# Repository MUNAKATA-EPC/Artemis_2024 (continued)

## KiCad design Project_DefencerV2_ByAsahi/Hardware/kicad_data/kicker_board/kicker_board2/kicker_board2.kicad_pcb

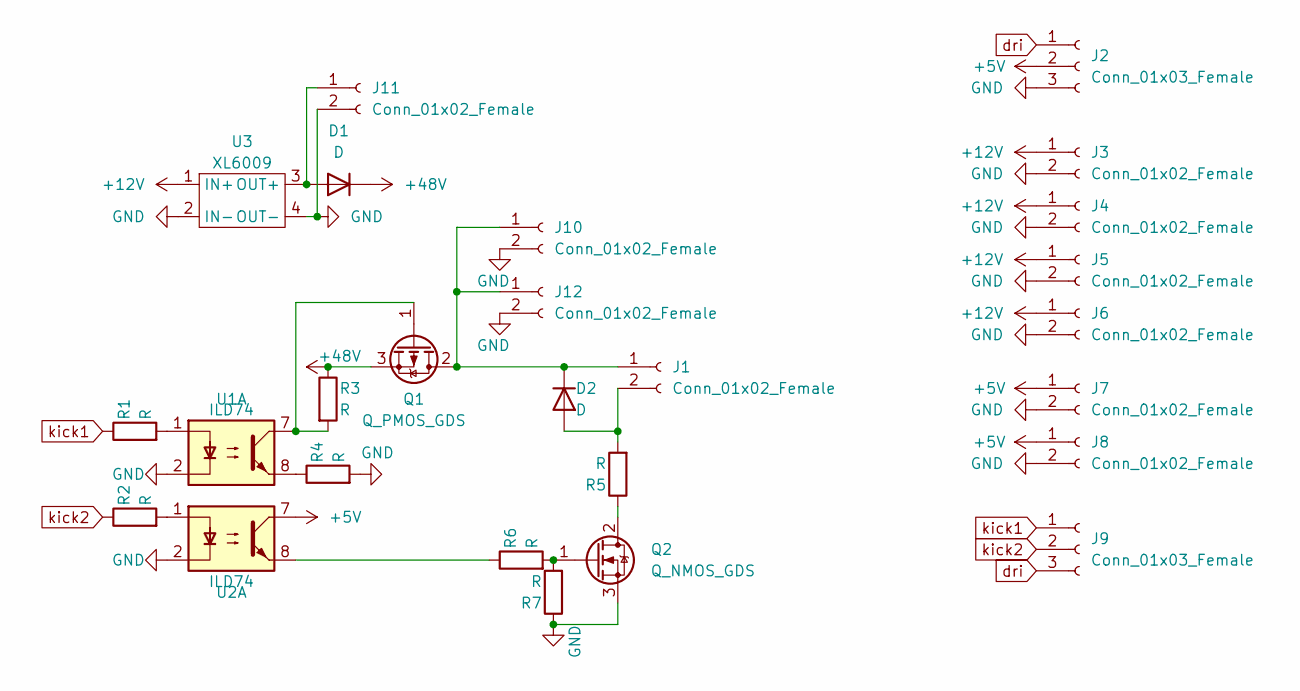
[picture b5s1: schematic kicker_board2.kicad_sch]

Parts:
D1, D2: D; D_5W_P10.16mm_Horizontal
J1, J3, J4, J5, J6, J7, J8, J10, J11, J12: Conn_01x02_Female; JST_XH_B2B-XH-A_1x02_P2.50mm_Vertical
J2, J9: Conn_01x03_Female; JST_XH_B3B-XH-A_1x03_P2.50mm_Vertical
Q1: Q_PMOS_GDS; Nch MOSFET
Q2: Q_NMOS_GDS; Nch MOSFET
R1, R2, R3, R4, R6, R7: R; R_Axial_DIN0204_L3.6mm_D1.6mm_P5.08mm_Horizontal
R5: R; R_Axial_Power_L25.0mm_W9.0mm_P10.16mm_Vertical
U1, U2: ILD74; フォトカプラー
U3: XL6009

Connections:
+5V: J2.2, J7.1, J8.1, U2.7
+12V: J3.1, J4.1, J5.1, J6.1, U3.1 (IN+)
+48V: D1.1 (K), Q1.3 (S), R3.1
GND: J2.3, J3.2, J4.2, J5.2, J6.2, J7.2, J8.2, J10.2, J11.2, J12.2, Q2.3 (S), R4.2, R7.1, U1.2, U2.2, U3.2 (IN-), U3.4 (OUT-)
unnamed: D1.2 (A), J11.1, U3.3 (OUT+)
unnamed: D2.1 (K), J1.1, J10.1, J12.1, Q1.2 (D)
unnamed: D2.2 (A), J1.2, R5.2
unnamed: Q1.1 (G), R3.2, U1.7
unnamed: Q2.1 (G), R6.2, R7.2
unnamed: Q2.2 (D), R5.1
unnamed: R1.2, U1.1
unnamed: R2.2, U2.1
unnamed: R4.1, U1.8
unnamed: R6.1, U2.8
dri: J2.1, J9.3
kick1: J9.1, R1.1
kick2: J9.2, R2.1

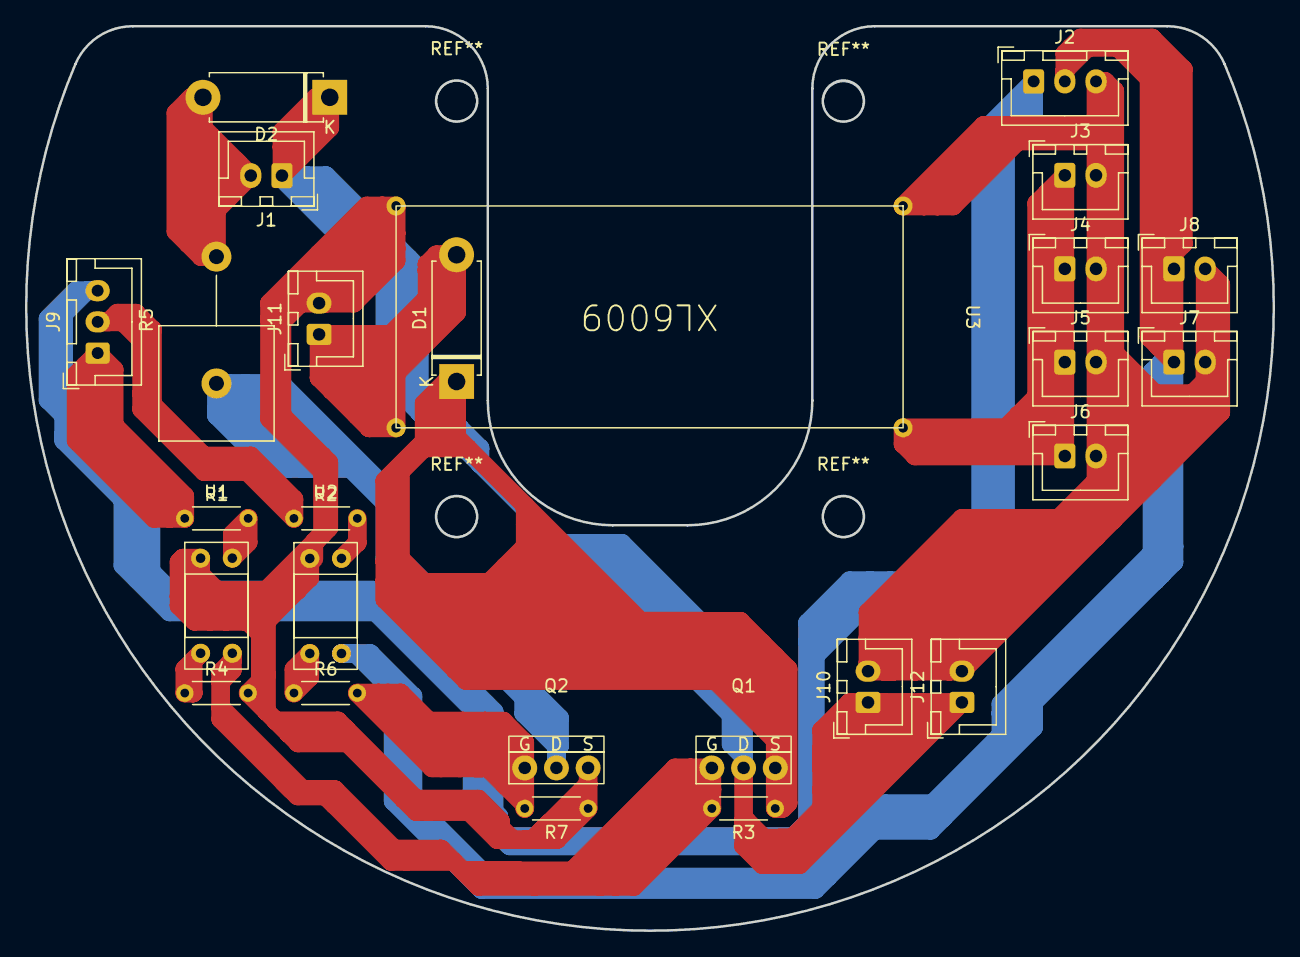
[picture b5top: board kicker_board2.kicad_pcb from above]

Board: 2 copper layers, 100.0 x 72.5 mm, 26 parts (0 on the bottom side), 17 nets.

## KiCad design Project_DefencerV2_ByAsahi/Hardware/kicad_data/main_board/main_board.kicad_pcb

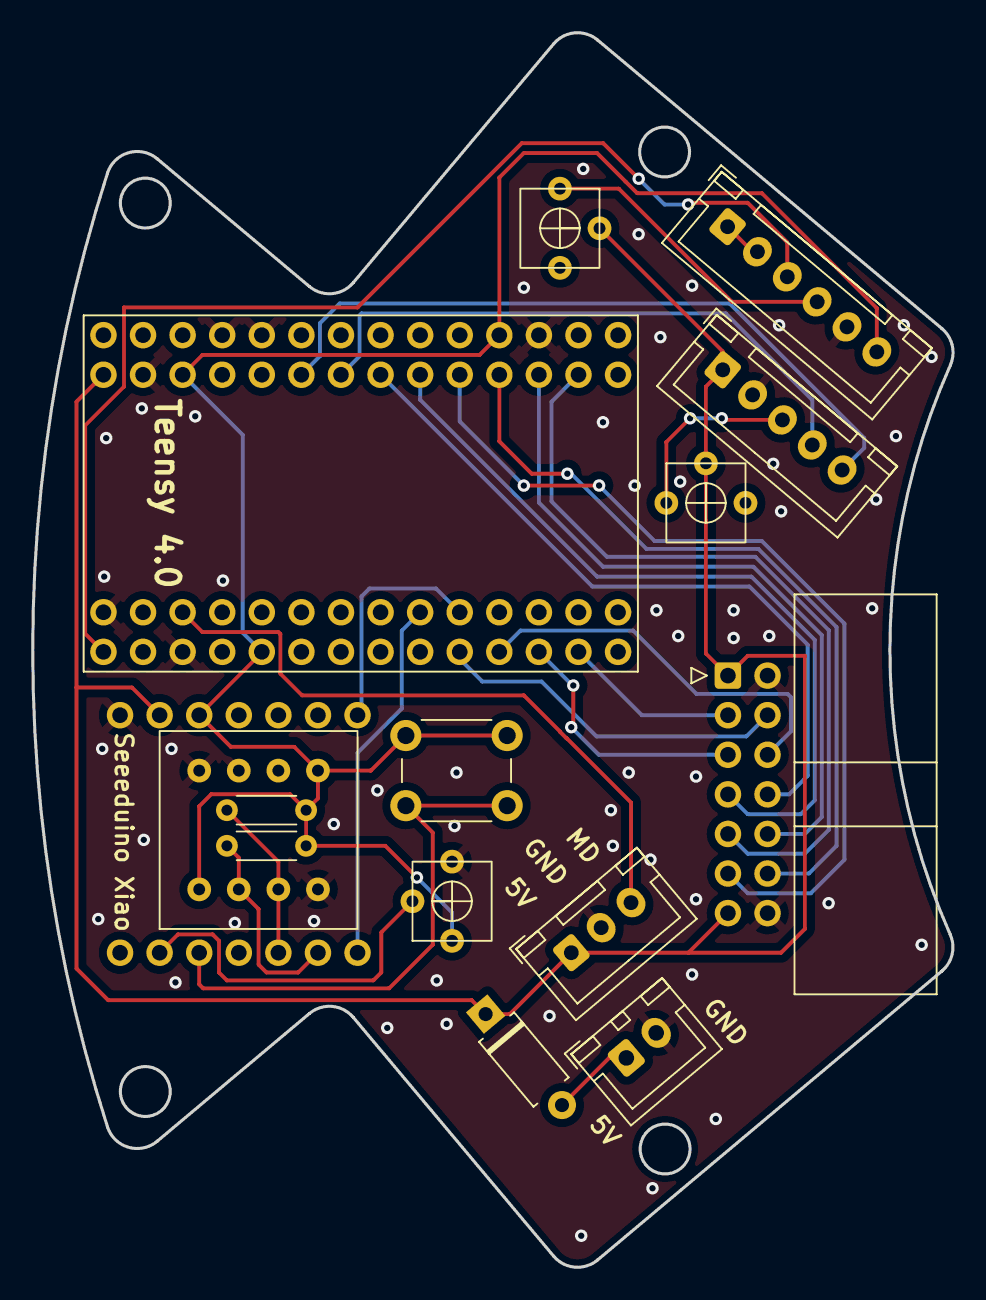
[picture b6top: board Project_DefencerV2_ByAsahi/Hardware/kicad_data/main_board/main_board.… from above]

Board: 2 copper layers, 59.1 x 79.2 mm, 15 parts (0 on the bottom side), 27 nets.

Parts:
D1: D; D_A-405_P7.62mm_Horizontal
J1: Conn_01x02_Female; JST_XH_B2B-XH-A_1x02_P2.50mm_Vertical
J2: Conn_01x03_Female; JST_XH_B3B-XH-A_1x03_P2.50mm_Vertical
J3: Conn_01x05_Female; JST_XH_B5B-XH-A_1x05_P2.50mm_Vertical
J4: Conn_01x14_Female; IDC-Header_2x07_P2.54mm_Horizontal
J5: Conn_01x06_Female; JST_XH_B6B-XH-A_1x06_P2.50mm_Vertical
R1, R2: R_Trim; Variable_Register
R3, R4: R; R_Axial_DIN0204_L3.6mm_D1.6mm_P5.08mm_Horizontal
RV1: R_Potentiometer_Trim_US; Variable_Register
SW1: SW_Push; SW_PUSH_6mm_H5mm
U1: Teensy4.0; Teensy_Brakeout
U2: SeeeduinoXIAO; seeeduinoXIAO
U3: L3GD20H_module; L3GD20H_Module_KiCad6.0

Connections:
+3.3V: J5.6, R3.2, R4.2, RV1.1, SW1.1, U1.31 (3V3), U2.12 (3V3), U3.1 (VCC), U3.8 (CS)
+5V: D1.1 (K), J2.1, J3.1, J4.1, J4.13, R1.2, R2.2, U1.33 (VIN), U2.13 (GND)
A1: RV1.2, U2.2 (PA4_A1_D1)
A2: SW1.2, U2.3 (PA10_A2_D2)
Ball_Seeed_Rx: J4.10, U1.22 (15_A1_RX3_SPDIF_IN)
Ball_Seeed_Tx: J4.9, U1.21 (14_A0_TX3_SPDIF_OUT)
GND: J1.2, J2.2, J3.2, J4.2, J4.14, J5.5, RV1.3, U1.1 (GND), U2.14 (5V), U3.4 (SA0), U3.5 (GND), U3.6 (INT1), U3.7 (INT2)
Gyro_Seeed_Rx: U1.9 (7_RX2_OUT1A), U2.7 (PB08_A6_D6_TX)
Gyro_Seeed_Tx: U1.10 (8_TX2_IN1), U2.8 (PB09_A7_D7_RX)
Kathode: J5.1, J5.2
L3GD20H_SCL: R3.1, U2.6 (PA9_A5_D5_SCL), U3.2 (SCL)
L3GD20H_SDA: R4.1, U2.5 (PA8_A4_D4_SDA), U3.3 (SDA)
Line_Seeed_Rx: J3.5, U1.28 (21_A7_RX5_BCLK1)
Line_Seeed_Tx: J3.4, U1.27 (20_A6_TX5_LRCLK1)
MD_TX: J2.3, U1.3 (1_TX1_CTX2_MISO1)
unnamed: D1.2 (A), J1.1
unnamed: J3.3, R1.1
unnamed: J5.4, R2.1
OpenMV_Rx: J4.12, U1.23 (16_A2_RX4_SCL1)
OpenMV_Tx: J4.11, U1.24 (17_A3_TX4_SDA1)
Push_Enter: J4.3, U1.41 (30_CRX3)
Push_Left: J4.4, U1.42 (31_CTX3)
Push_Right: J4.5, U1.43 (32_OUT1B)
SSD1306_SCL: J4.8, U1.26 (19_A5_SCL0)
SSD1306_SDA: J4.7, U1.25 (18_A4_SDA0)
Toggle_Switch: J4.6, U1.44 (33_MCLK2)
TouchSensor: J5.3, U1.45 (34_DAT1_MISO2)

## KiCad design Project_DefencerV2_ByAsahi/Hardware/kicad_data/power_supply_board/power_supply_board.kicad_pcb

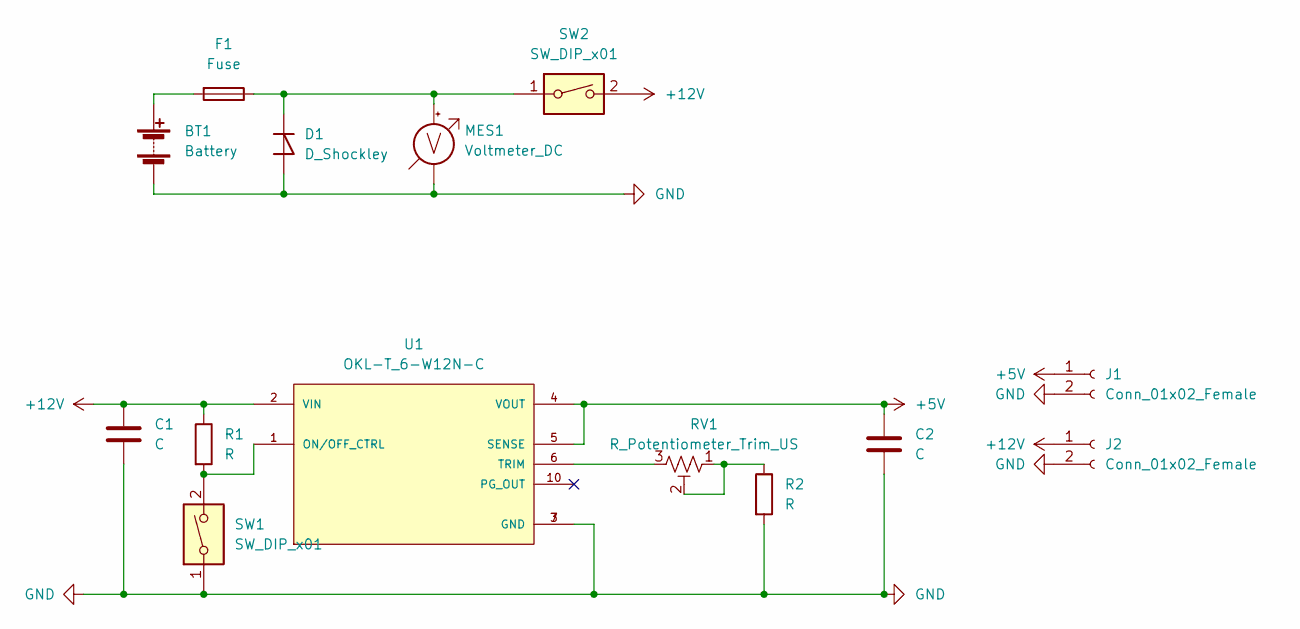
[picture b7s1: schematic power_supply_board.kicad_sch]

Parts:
BT1: Battery; JST_VH_B2P-VH_1x02_P3.96mm_Vertical
C1, C2: C; C_Disc_D5.1mm_W3.2mm_P5.00mm
D1: D_Shockley; D_5W_P12.70mm_Horizontal
F1: Fuse; fuse_socket
J1, J2: Conn_01x02_Female; JST_XH_B2B-XH-A_1x02_P2.50mm_Vertical
MES1: Voltmeter_DC; voltage_counter
R1, R2: R; R_Axial_DIN0204_L3.6mm_D1.6mm_P5.08mm_Horizontal
RV1: R_Potentiometer_Trim_US; Potentiometer_Bourns_3296W_Vertical
SW1: SW_DIP_x01; TA48033S
SW2: SW_DIP_x01; DS-850k
U1: OKL-T_6-W12N-C; DCDC-murata-6A

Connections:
+5V: C2.1, J1.1, U1.4 (VOUT), U1.5 (SENSE)
+12V: C1.1, J2.1, R1.1, SW2.2, U1.2 (VIN)
GND: BT1.2 (-), C1.2, C2.2, D1.2 (A), J1.2, J2.2, MES1.1 (-), R2.2, SW1.1, U1.3 (GND), U1.7 (GND)
unnamed: BT1.1 (+), F1.2
unnamed: D1.1 (K), F1.1, MES1.2 (+), SW2.1
unnamed: R1.2, SW1.2, U1.1 (ON/OFF_CTRL)
unnamed: R2.1, RV1.1, RV1.2
unnamed: RV1.3, U1.6 (TRIM)

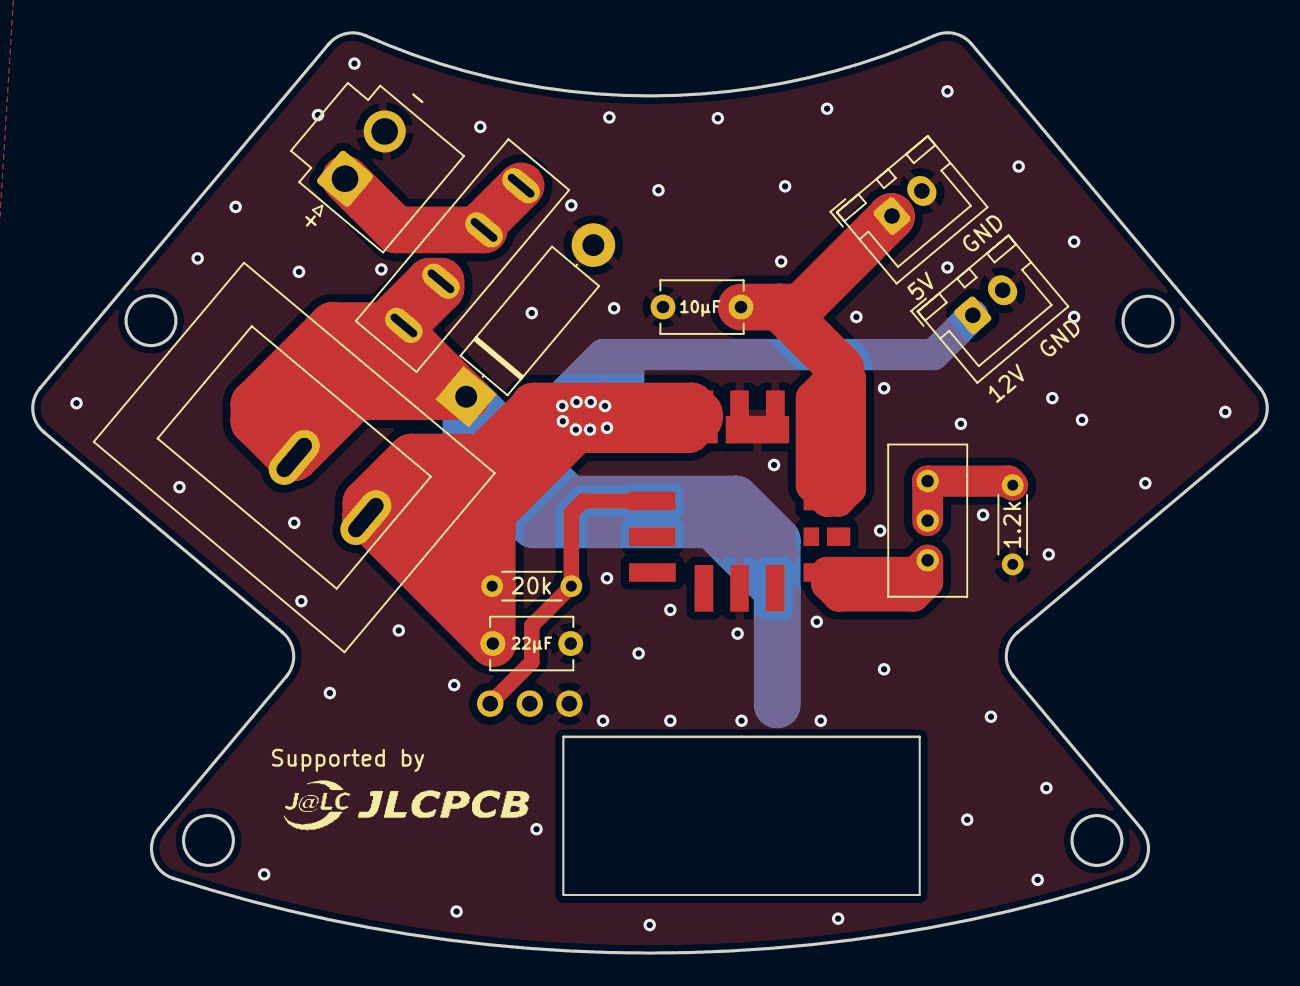
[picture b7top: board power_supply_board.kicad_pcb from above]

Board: 2 copper layers, 79.2 x 59.1 mm, 14 parts (0 on the bottom side), 8 nets.
